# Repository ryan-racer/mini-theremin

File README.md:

# Mini-Theremin

A Mini-Theremin PCB designed as part of an electronics course project. A theremin is a musical instrument played without physical contact — this compact version uses a capacitive touch pad to control audio frequency through a Schmitt Trigger oscillator.

## How It Works

The Mini-Theremin uses a copper touch pad as one half of a capacitor. When you bring your hand near or touch the pad, you change the system's capacitance, which alters the oscillation frequency of a Schmitt Trigger oscillator built around an LM358 op-amp. The oscillator output drives a 2N7000 MOSFET that switches a speaker on and off at the oscillation frequency, producing an audible tone. Moving your hand closer to the pad lowers the pitch; moving it away raises it.

## 3D Board View

## Completed Build

| Front | Back |
|-------|------|
|  |  |

## Bill of Materials

| Reference | Qty | Value | Component |
|-----------|-----|-------|-----------|
| Cbase1 | 1 | 220 pF | Base capacitor |
| Cbulk1 | 1 | 10 uF | Bulk decoupling capacitor |
| Cdec1, Cref1 | 2 | 0.1 uF | Decoupling/reference capacitors |
| J1 | 1 | Conn_01x02 | 2-pin power connector |
| LS1 | 1 | Speaker | Piezo speaker |
| Q1 | 1 | 2N7000 | N-channel MOSFET |
| R3, R4, Rg1, Rpd1 | 4 | 100 kOhm | Resistors |
| Rf1 | 1 | 200 kOhm | Feedback resistor |
| Rgate1, RLS1 | 2 | 100 Ohm | Gate/load resistors |
| Rosc1 | 1 | 2.2 MOhm | Oscillation resistor |
| TOUCH_PAD1 | 1 | TOUCH_PAD | 30x30mm capacitive touch pad |
| U1 | 1 | LM358 | Dual op-amp (Schmitt trigger) |

## Files

- `Theremin.kicad_sch` - KiCad schematic
- `Theremin.kicad_pcb` - KiCad PCB layout
- `Theremin.kicad_pro` - KiCad project file
- `240Library/` - Custom component library (footprints and symbols)
- `Therminim.pretty/` - Custom touch pad footprint
- `PCB_Lab_Report.pdf` - Lab report with design documentation
- `*.gbr` / `*.drl` - Gerber files and drill files for manufacturing

## Software

Designed in [KiCad 9.0](https://www.kicad.org/).

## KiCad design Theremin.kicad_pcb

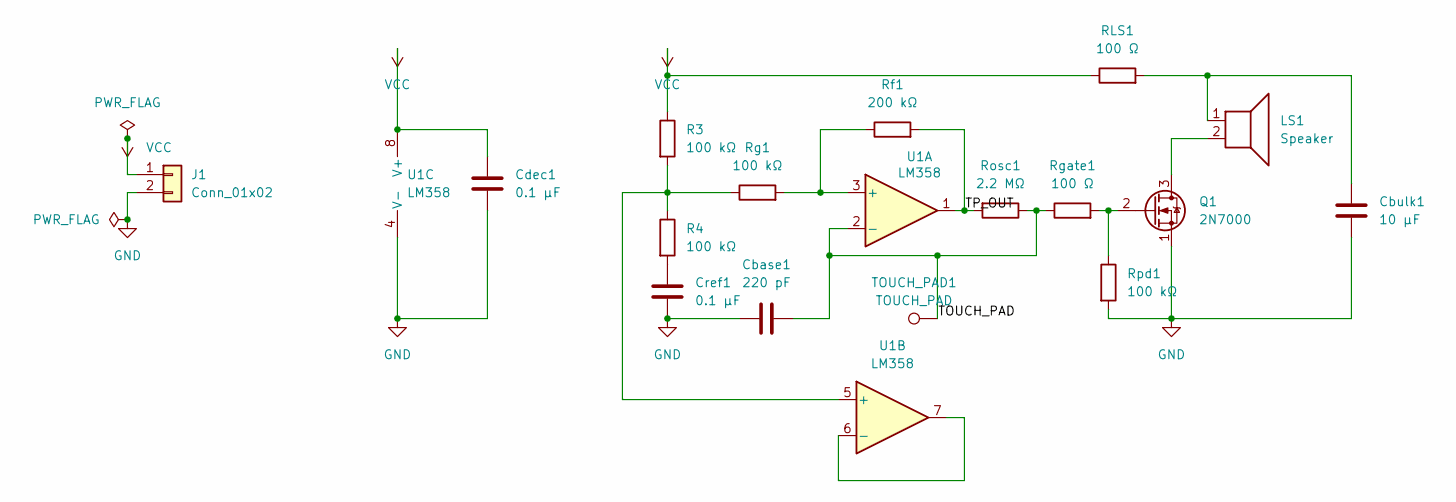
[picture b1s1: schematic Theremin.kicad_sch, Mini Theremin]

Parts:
Cbase1: 220 pF; CAP_YX_6P3X11_RUB
Cbulk1: 10 µF; CAP_YX_6P3X11_RUB
Cdec1: 0.1 µF; CAP_YX_6P3X11_RUB
Cref1: 0.1 µF; CAP_YX_6P3X11_RUB
J1: Conn_01x02; HARWIN_M20-9990246
LS1: Speaker; XDCR_AT-1224-TWT-5V-2-R
Q1: 2N7000; TO220AB_VIS
R3, R4: 100 kΩ; K104K10X7RF5UH5_VIS
RLS1: 100 Ω; K104K10X7RF5UH5_VIS
Rf1: 200 kΩ; K104K10X7RF5UH5_VIS
Rg1: 100 kΩ; K104K10X7RF5UH5_VIS
Rgate1: 100 Ω; K104K10X7RF5UH5_VIS
Rosc1: 2.2 MΩ; K104K10X7RF5UH5_VIS
Rpd1: 100 kΩ; K104K10X7RF5UH5_VIS
TOUCH_PAD1: TOUCH_PAD; Touch_Pad_30x30mm
U1: LM358; DIP794W45P254L959H508Q8

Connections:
/TOUCH_PAD: Cbase1.2, Rgate1.1, Rosc1.1, TOUCH_PAD1.1, U1.2 (-)
/TP_OUT: Rf1.2, Rosc1.2, U1.1
GND: Cbase1.1, Cbulk1.2, Cdec1.2, Cref1.2, J1.2, Q1.1 (S), Rpd1.2, U1.4 (V-)
unnamed: Cbulk1.1, LS1.1, RLS1.2
unnamed: Cref1.1, R4.2
unnamed: LS1.2, Q1.3 (D)
unnamed: Q1.2 (G), Rgate1.2, Rpd1.1
unnamed: Rf1.1, Rg1.2, U1.3 (+)
unnamed: R3.2, R4.1, Rg1.1, U1.5 (+)
unnamed: U1.6 (-), U1.7
VCC: Cdec1.1, J1.1, R3.1, RLS1.1, U1.8 (V+)

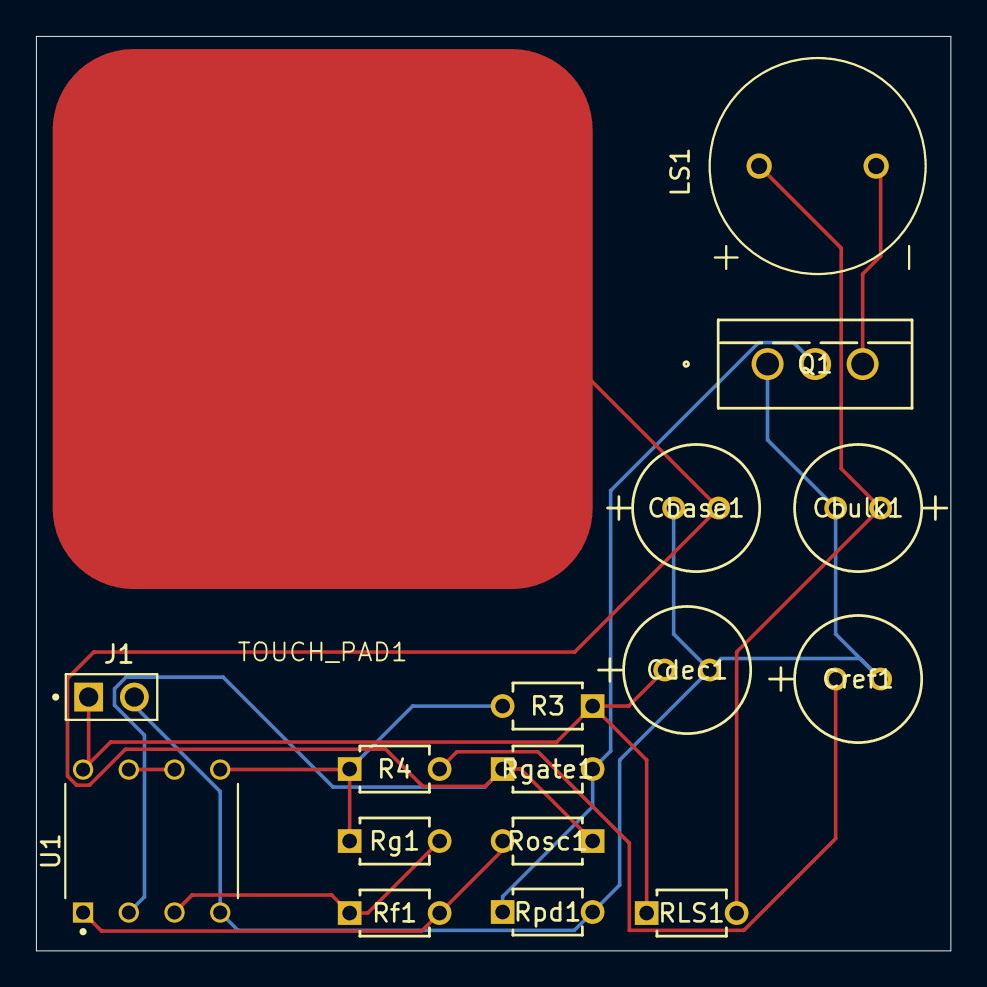
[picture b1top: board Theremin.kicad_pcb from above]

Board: 2 copper layers, 50.8 x 50.8 mm, 17 parts (0 on the bottom side), 11 nets.

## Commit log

2026-04-15 Initial commit: Mini-Theremin PCB project
    KiCad PCB design for a capacitive touch Mini-Theremin with schematic,
    PCB layout, Gerber files, component library, and lab report.
2026-04-15 Remove schematic image from README
